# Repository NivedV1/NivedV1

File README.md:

- 👋 Hi, I’m Nived
- 👀 I’m interested in ...
- 🌱 I’m currently learning ...
- N❤️

<!---
NivedV1/NivedV1 is a ✨ special ✨ repository because its `README.md` (this file) appears on your GitHub profile.
You can click the Preview link to take a look at your changes.
--->

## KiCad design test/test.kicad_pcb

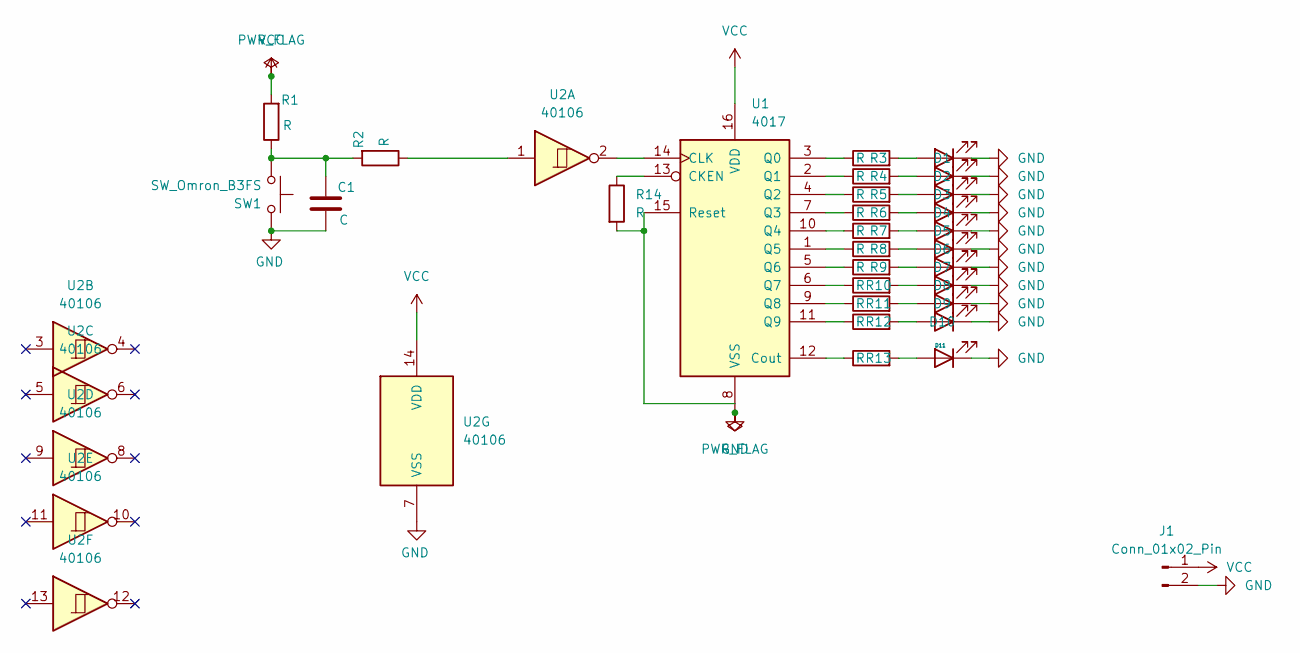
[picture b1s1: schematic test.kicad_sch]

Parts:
C1: C; C_Disc_D3.0mm_W1.6mm_P2.50mm
D1, D2, D3, D4, D5, D6, D7, D8, D9, D10, D11: LED; LED_D4.0mm
J1: Conn_01x02_Pin; PinHeader_1x02_P1.00mm_Vertical
R1, R2, R3, R4, R5, R6, R7, R8, R9, R10, R11, R12, R13, R14: R; R_Axial_DIN0309_L9.0mm_D3.2mm_P20.32mm_Horizontal
SW1: SW_Omron_B3FS; SW_PUSH_6mm
U1: 4017; DIP-16_W7.62mm
U2: 40106; DIP-14_W7.62mm

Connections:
GND: C1.2, D1.1 (K), D2.1 (K), D3.1 (K), D4.1 (K), D5.1 (K), D6.1 (K), D7.1 (K), D8.1 (K), D9.1 (K), D10.1 (K), D11.1 (K), J1.2, SW1.2, U1.8 (VSS), U2.7 (VSS)
unnamed: C1.1, R1.1, R2.2, SW1.1
unnamed: D1.2 (A), R3.2
unnamed: D2.2 (A), R4.2
unnamed: D3.2 (A), R5.2
unnamed: D4.2 (A), R6.2
unnamed: D5.2 (A), R7.2
unnamed: D6.2 (A), R8.2
unnamed: D7.2 (A), R9.2
unnamed: D8.2 (A), R10.2
unnamed: D9.2 (A), R11.2
unnamed: D10.2 (A), R12.2
unnamed: D11.2 (A), R13.2
unnamed: R2.1, U2.1
unnamed: R14.1, U1.13 (CKEN)
unnamed: U1.14 (CLK), U2.2
unnamed: R13.1, U1.12 (Cout)
unnamed: R3.1, U1.3 (Q0)
unnamed: R4.1, U1.2 (Q1)
unnamed: R5.1, U1.4 (Q2)
unnamed: R6.1, U1.7 (Q3)
unnamed: R7.1, U1.10 (Q4)
unnamed: R8.1, U1.1 (Q5)
unnamed: R9.1, U1.5 (Q6)
unnamed: R10.1, U1.6 (Q7)
unnamed: R11.1, U1.9 (Q8)
unnamed: R12.1, U1.11 (Q9)
unnamed: R14.2, U1.15 (Reset)
VCC: J1.1, R1.2, U1.16 (VDD), U2.14 (VDD)

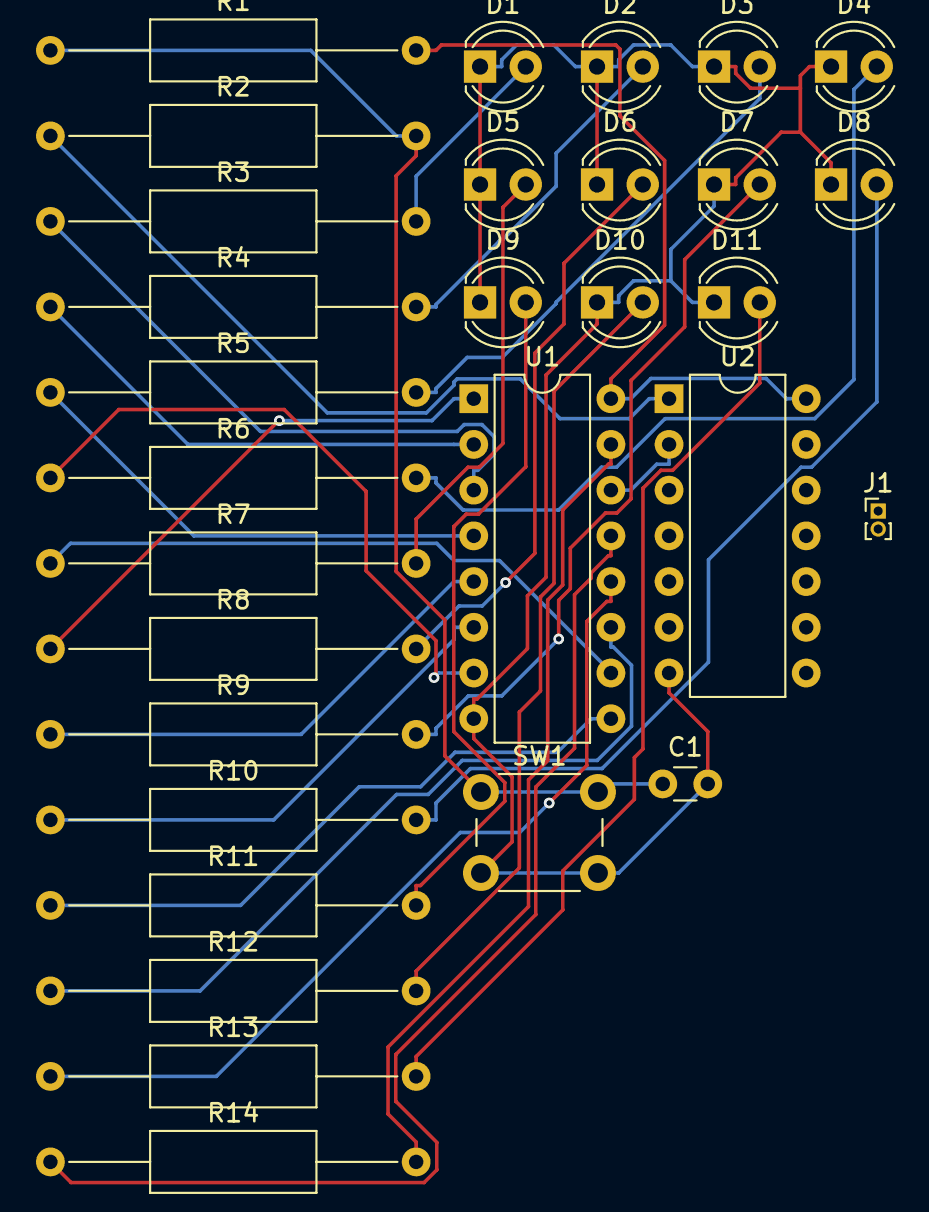
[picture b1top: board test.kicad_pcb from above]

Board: 2 copper layers, 30 parts (0 on the bottom side), 29 nets.

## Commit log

2025-07-12 Create CNAME
2025-09-23 n
    hb
2025-09-23 dsaf
2025-09-27 ';fg '
2025-09-27 hj
    vbn
2025-09-27 name cgane
2025-09-27 ffgf
2025-09-27 cdfs
2025-09-27 dsas
2025-09-27 gfh ghf
2025-10-04 nodejs upload with index
2025-10-05 delte node
2025-10-07 removed photos
2025-10-07 added iamgws
